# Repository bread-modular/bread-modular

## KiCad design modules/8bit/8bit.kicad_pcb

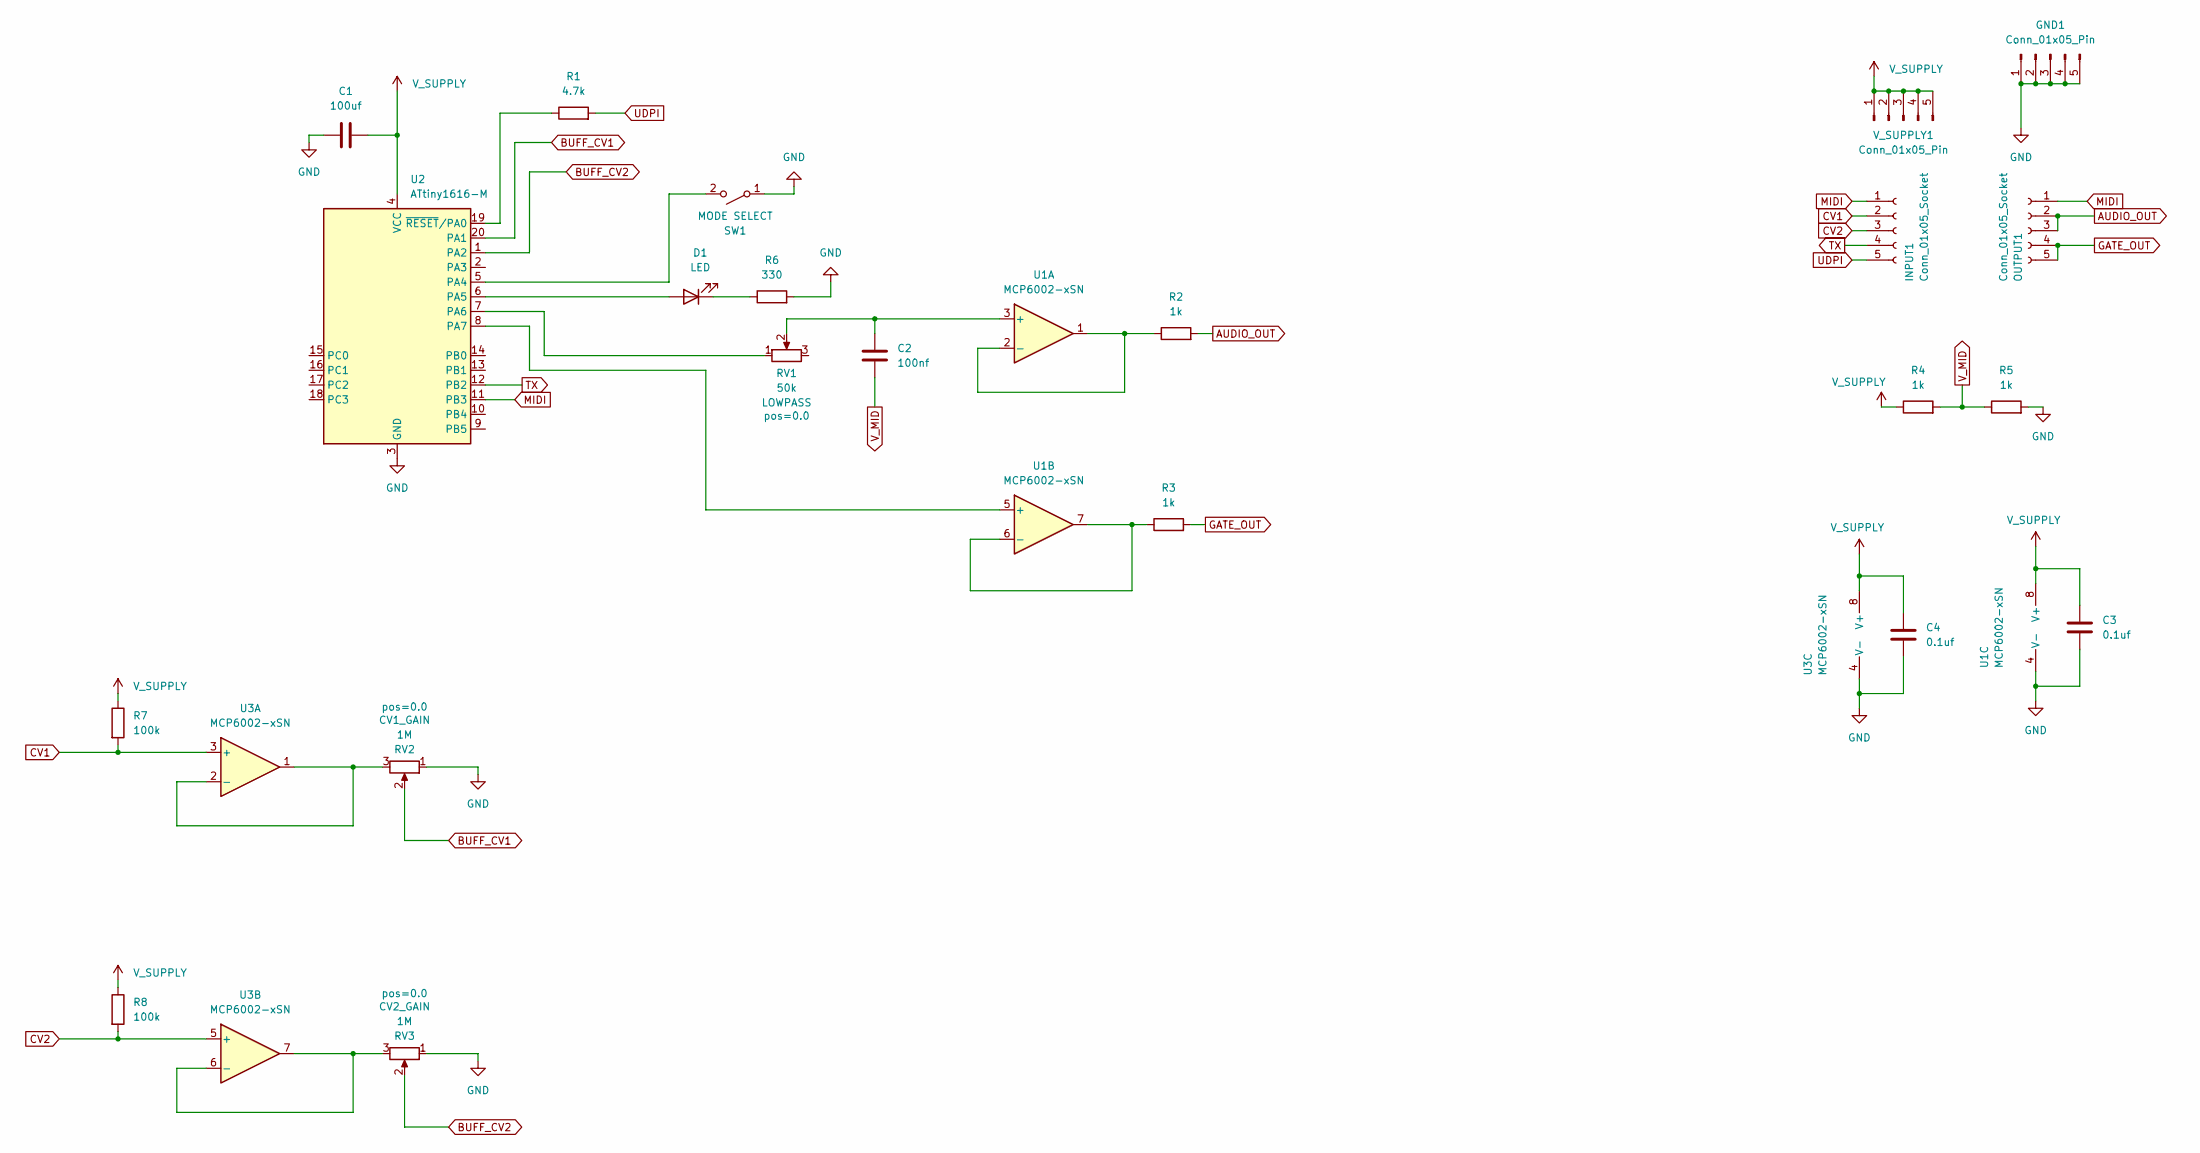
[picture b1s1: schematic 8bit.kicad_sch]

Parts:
C1: 100uf; C_1206_3216Metric
C2: 100nf; C_0402_1005Metric
C3, C4: 0.1uf; C_0402_1005Metric
D1: LED; LED_0603_1608Metric
GND1: Conn_01x05_Pin; Power_Connector
INPUT1: Conn_01x05_Socket; PinSocket_1x05_P2.54mm_Vertical
OUTPUT1: Conn_01x05_Socket; PinSocket_1x05_P2.54mm_Vertical
R1: 4.7k; R_0402_1005Metric
R2, R3, R4, R5: 1k; R_0402_1005Metric
R6: 330; R_0402_1005Metric
R7, R8: 100k; R_0402_1005Metric
RV1: 50k; Potentiometer_RV09
RV2, RV3: 1M; Potentiometer_RV09
SW1: MODE SELECT; SPST_TS-1187A-B-A-B
U1, U3: MCP6002-xSN; SOIC-8-1EP_3.9x4.9mm_P1.27mm_EP2.29x3mm
U2: ATtiny1616-M; VQFN-20-1EP_3x3mm_P0.4mm_EP1.7x1.7mm
V_SUPPLY1: Conn_01x05_Pin; Power_Connector

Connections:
AUDIO_OUT: OUTPUT1.2, OUTPUT1.3, R2.2
BUFF_CV1: RV2.2, U2.20 (PA1)
BUFF_CV2: RV3.2, U2.1 (PA2)
CV1: INPUT1.2, R7.2, U3.3 (+)
CV2: INPUT1.3, R8.2, U3.5 (+)
GATE_OUT: OUTPUT1.4, OUTPUT1.5, R3.2
GND: C1.1, C3.2, C4.2, GND1.1, GND1.2, GND1.3, GND1.4, GND1.5, R5.2, R6.2, RV2.1, RV3.1, SW1.1 (A), U1.4 (V-), U2.3 (GND), U2.21 (GND), U3.4 (V-)
MIDI: INPUT1.1, OUTPUT1.1, U2.11 (PB3)
unnamed: D1.2 (A), U2.6 (PA5)
unnamed: D1.1 (K), R6.1
unnamed: SW1.2 (B), U2.5 (PA4)
unnamed: C2.2, RV1.2, U1.3 (+)
unnamed: R2.1, U1.1, U1.2 (-)
unnamed: U1.5 (+), U2.8 (PA7)
unnamed: R3.1, U1.6 (-), U1.7
unnamed: RV1.1, U2.7 (PA6)
unnamed: R1.1, U2.19 (~RESET/PA0)
unnamed: RV2.3, U3.1, U3.2 (-)
unnamed: RV3.3, U3.6 (-), U3.7
TX: INPUT1.4, U2.12 (PB2)
UDPI: INPUT1.5, R1.2
V_MID: C2.1, R4.2, R5.1
V_SUPPLY: C1.2, C3.1, C4.1, R4.1, R7.1, R8.1, U1.8 (V+), U2.4 (VCC), U3.8 (V+), V_SUPPLY1.1, V_SUPPLY1.2, V_SUPPLY1.3, V_SUPPLY1.4, V_SUPPLY1.5

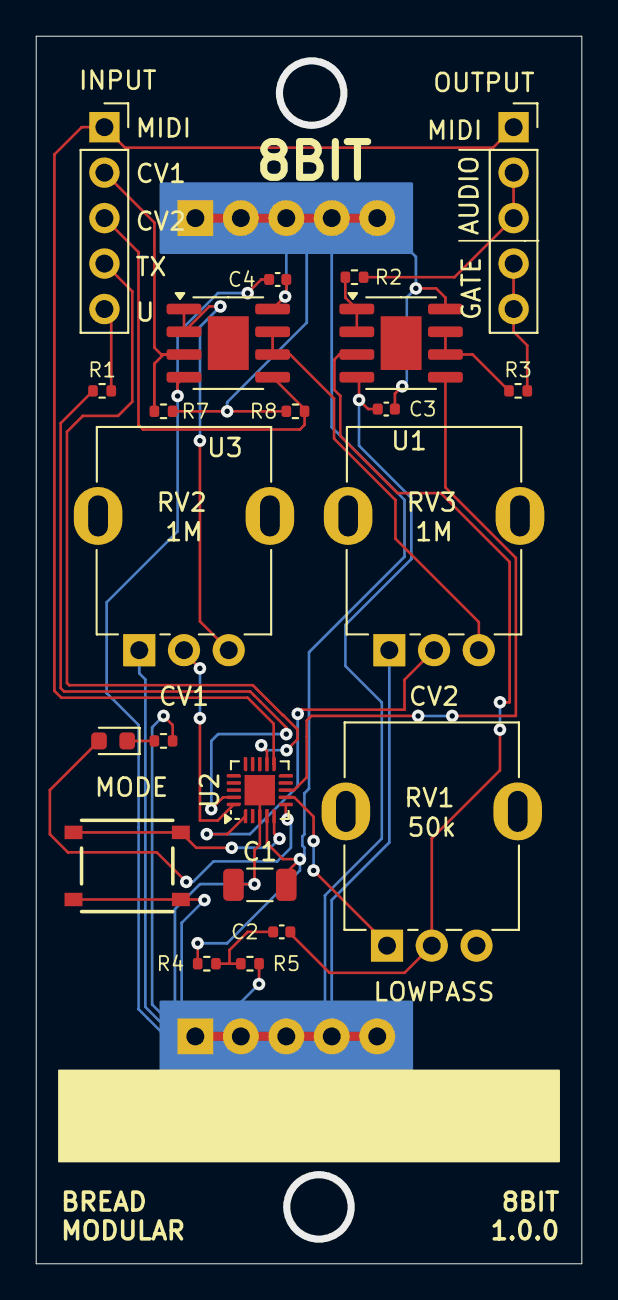
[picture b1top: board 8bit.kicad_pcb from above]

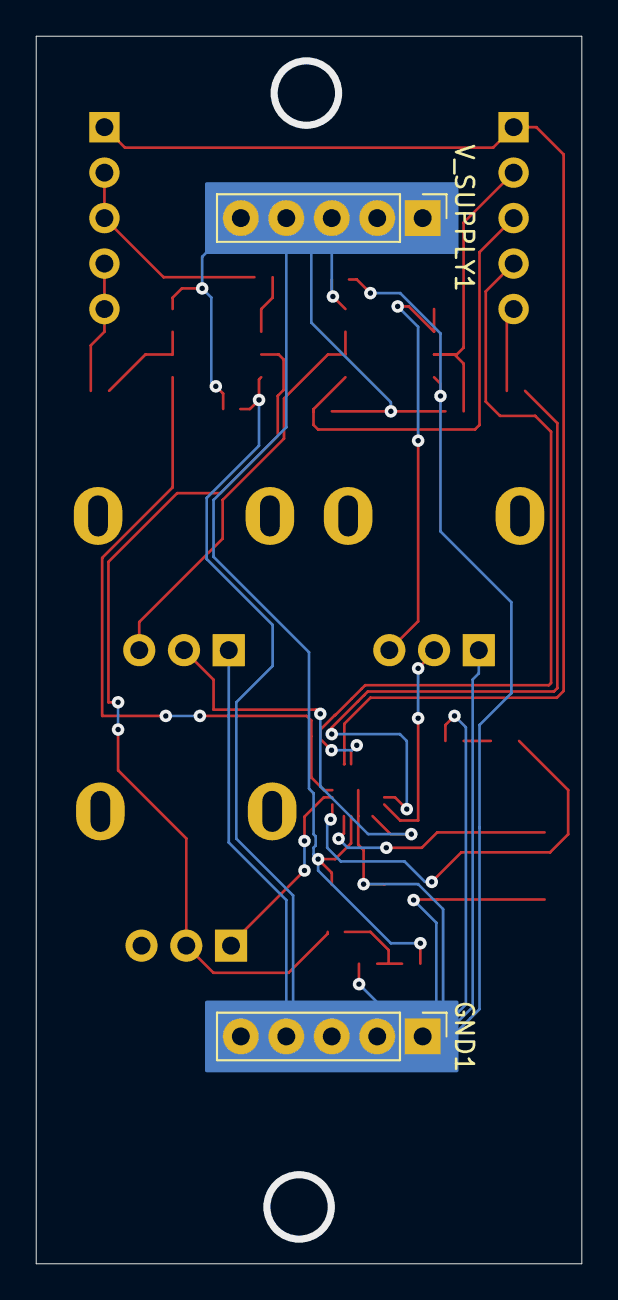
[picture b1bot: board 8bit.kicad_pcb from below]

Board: 2 copper layers, 30.5 x 68.6 mm, 24 parts (2 on the bottom side), 23 nets.

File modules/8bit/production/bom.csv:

Designator,Footprint,Quantity,Value,LCSC Part #
C1,1206,1,100uf,
C2,0402,1,100nf,
"C3, C4",0402,2,0.1uf,
D1,0603,1,LED,
"GND1, V_SUPPLY1",Power_Connector,2,Conn_01x05_Pin,
"INPUT1, OUTPUT1",PinSocket_1x05_P2.54mm_Vertical,2,Conn_01x05_Socket,
R1,0402,1,4.7k,
"R2, R3, R4, R5",0402,4,1k,
R6,0402,1,330,
"R7, R8",0402,2,100k,
RV1,Potentiometer_RV09,1,50k,
"RV2, RV3",Potentiometer_RV09,2,1M,
SW1,SPST_TS-1187A-B-A-B,1,MODE SELECT,
"U1, U3",SOIC-8-1EP_3.9x4.9mm_P1.27mm_EP2.29x3mm,2,MCP6002-xSN,
U2,VQFN-20-1EP_3x3mm_P0.4mm_EP1.7x1.7mm,1,ATtiny1616-M,

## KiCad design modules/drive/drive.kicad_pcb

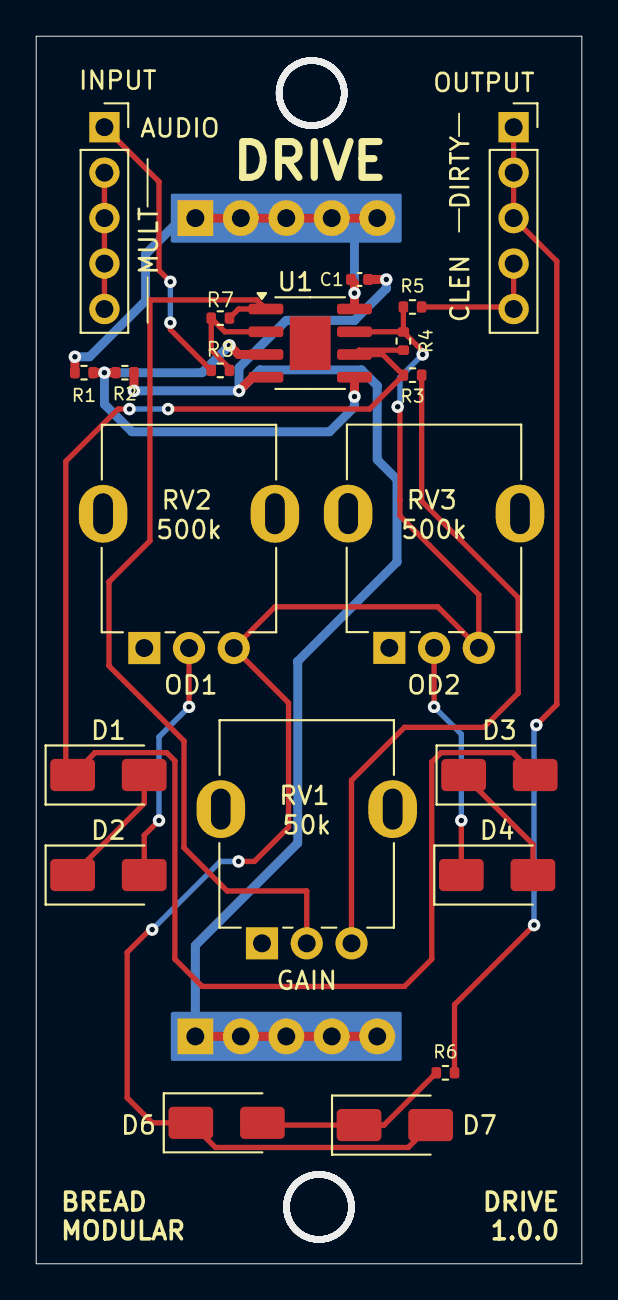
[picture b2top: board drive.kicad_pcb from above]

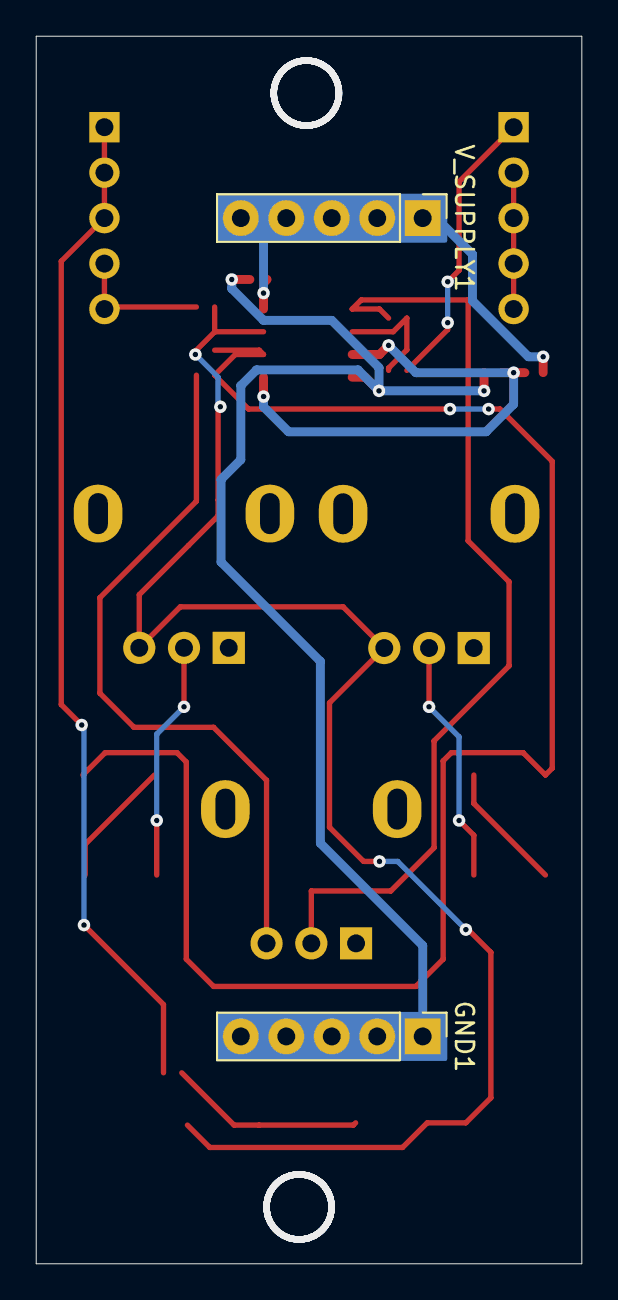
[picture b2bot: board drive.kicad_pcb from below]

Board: 2 copper layers, 30.5 x 68.6 mm, 23 parts (2 on the bottom side), 17 nets.

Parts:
C1: 0.1uf; C_0402_1005Metric
D1, D2, D3, D4, D7: SS14; D_SMA
D6: SS210; D_SMA
GND1: Conn_01x05_Pin; Power_Connector
INPUT1: Conn_01x05_Socket; PinSocket_1x05_P2.54mm_Vertical
OUTPUT1: Conn_01x05_Socket; PinSocket_1x05_P2.54mm_Vertical
R1, R2, R3, R5, R6: 1k; R_0402_1005Metric
R4: 51k; R_0402_1005Metric
R7, R8: 100k; R_0402_1005Metric
RV1: 50k; Potentiometer_RV09
RV2, RV3: 500k; Potentiometer_RV09
U1: MCP6002-xSN; SOIC-8-1EP_3.9x4.9mm_P1.27mm_EP2.29x3mm
V_SUPPLY1: Conn_01x05_Pin; Power_Connector

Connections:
AUDIO_IN: INPUT1.1, R8.1
AUDIO_OUT_CLEAN: OUTPUT1.4, OUTPUT1.5, R5.2
AUDIO_OUT_DIRTY: OUTPUT1.1, OUTPUT1.2, OUTPUT1.3, R6.2
GND: C1.2, GND1.1, GND1.2, GND1.3, GND1.4, GND1.5, R2.2, U1.4 (V-)
unnamed: D1.2 (A), D2.1 (K)
unnamed: D1.1 (K), D3.2 (A), R3.2, R4.1, U1.6 (-)
unnamed: D2.2 (A), RV2.2
unnamed: D3.1 (K), D4.2 (A)
unnamed: D4.1 (K), RV3.2
unnamed: D6.2 (A), D7.1 (K), R6.1
unnamed: D6.1 (K), D7.2 (A), R4.2, R5.1, RV2.3, RV3.3, U1.7
unnamed: INPUT1.2, INPUT1.3, INPUT1.4, INPUT1.5
unnamed: R3.1, RV1.3
unnamed: R7.2, RV1.2, U1.1
unnamed: R7.1, R8.2, U1.2 (-)
V_MID: R1.2, R2.1, U1.3 (+), U1.5 (+)
V_SUPPLY: C1.1, R1.1, U1.8 (V+), V_SUPPLY1.1, V_SUPPLY1.2, V_SUPPLY1.3, V_SUPPLY1.4, V_SUPPLY1.5

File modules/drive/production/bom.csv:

Designator,Footprint,Quantity,Value,LCSC Part #
C1,0402,1,0.1uf,
"D1, D2, D3, D4, D7",D_SMA,5,SS14,
D6,D_SMA,1,SS210,
"GND1, V_SUPPLY1",Power_Connector,2,Conn_01x05_Pin,
"INPUT1, OUTPUT1",PinSocket_1x05_P2.54mm_Vertical,2,Conn_01x05_Socket,
"R1, R2, R3, R5, R6",0402,5,1k,
R4,0402,1,51k,
"R7, R8",0402,2,100k,
RV1,Potentiometer_RV09,1,50k,
"RV2, RV3",Potentiometer_RV09,2,500k,
U1,SOIC-8-1EP_3.9x4.9mm_P1.27mm_EP2.29x3mm,1,MCP6002-xSN,

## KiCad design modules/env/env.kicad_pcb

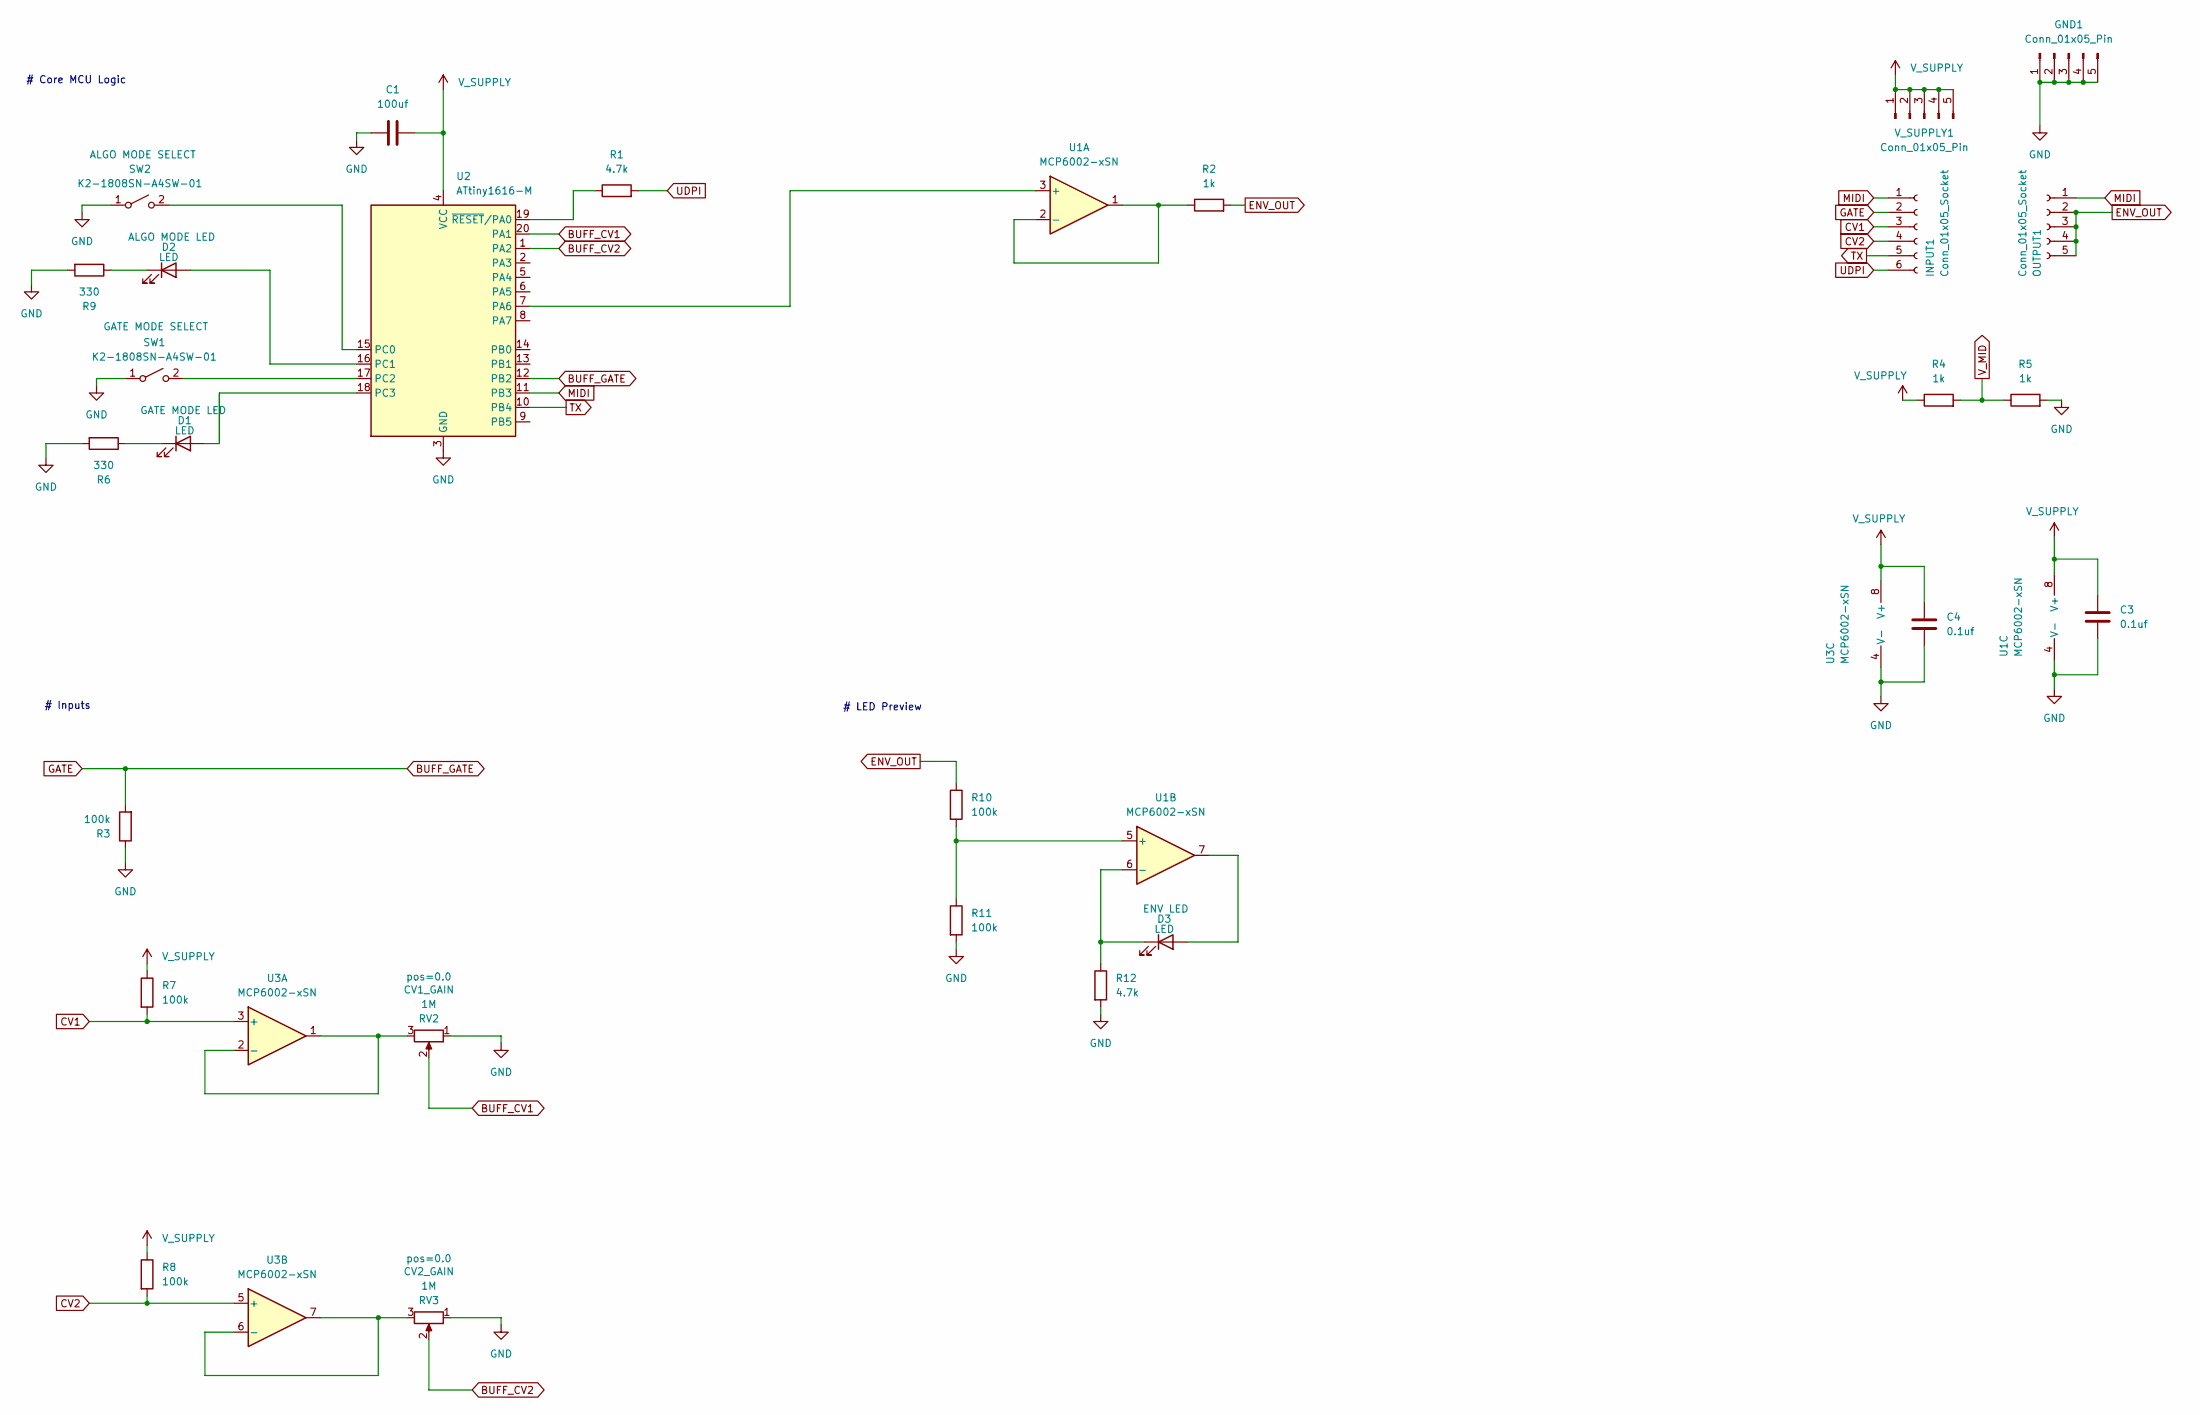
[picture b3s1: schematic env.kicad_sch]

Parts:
C1: 100uf; C_1206_3216Metric
C3, C4: 0.1uf; C_0402_1005Metric
D1, D2, D3: LED; LED_0603_1608Metric
GND1: Conn_01x05_Pin; Power_Connector
INPUT1: Conn_01x05_Socket; PinSocket_1x06_P2.54mm_Vertical
OUTPUT1: Conn_01x05_Socket; PinSocket_1x05_P2.54mm_Vertical
R1, R12: 4.7k; R_0402_1005Metric
R2, R4, R5: 1k; R_0402_1005Metric
R3, R7, R8, R10, R11: 100k; R_0402_1005Metric
R6, R9: 330; R_0402_1005Metric
RV2, RV3: 1M; Potentiometer_RV09
SW1, SW2: K2-1808SN-A4SW-01
U1, U3: MCP6002-xSN; SOIC-8-1EP_3.9x4.9mm_P1.27mm_EP2.29x3mm
U2: ATtiny1616-M; VQFN-20-1EP_3x3mm_P0.4mm_EP1.7x1.7mm
V_SUPPLY1: Conn_01x05_Pin; Power_Connector

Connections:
BUFF_CV1: RV2.2, U2.20 (PA1)
BUFF_CV2: RV3.2, U2.1 (PA2)
BUFF_GATE: INPUT1.2, R3.2, U2.12 (PB2)
CV1: INPUT1.3, R7.2, U3.3 (+)
CV2: INPUT1.4, R8.2, U3.5 (+)
ENV_OUT: OUTPUT1.2, OUTPUT1.3, OUTPUT1.4, OUTPUT1.5, R2.2, R10.1
GND: C1.1, C3.2, C4.2, GND1.1, GND1.2, GND1.3, GND1.4, GND1.5, R3.1, R5.2, R6.2, R9.2, R11.2, R12.2, RV2.1, RV3.1, SW1.1 (A), SW2.1 (A), U1.4 (V-), U2.3 (GND), U2.21 (GND), U3.4 (V-)
MIDI: INPUT1.1, OUTPUT1.1, U2.11 (PB3)
unnamed: D1.2 (A), U2.18 (PC3)
unnamed: D1.1 (K), R6.1
unnamed: D2.2 (A), U2.16 (PC1)
unnamed: D2.1 (K), R9.1
unnamed: D3.2 (A), U1.7
unnamed: D3.1 (K), R12.1, U1.6 (-)
unnamed: SW1.2 (B), U2.17 (PC2)
unnamed: SW2.2 (B), U2.15 (PC0)
unnamed: U1.3 (+), U2.7 (PA6)
unnamed: R2.1, U1.1, U1.2 (-)
unnamed: R10.2, R11.1, U1.5 (+)
unnamed: R1.1, U2.19 (~RESET/PA0)
unnamed: RV2.3, U3.1, U3.2 (-)
unnamed: RV3.3, U3.6 (-), U3.7
TX: INPUT1.5, U2.10 (PB4)
UDPI: INPUT1.6, R1.2
V_MID: R4.2, R5.1
V_SUPPLY: C1.2, C3.1, C4.1, R4.1, R7.1, R8.1, U1.8 (V+), U2.4 (VCC), U3.8 (V+), V_SUPPLY1.1, V_SUPPLY1.2, V_SUPPLY1.3, V_SUPPLY1.4, V_SUPPLY1.5

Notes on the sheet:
# LED Preview
# Core MCU Logic
# Inputs

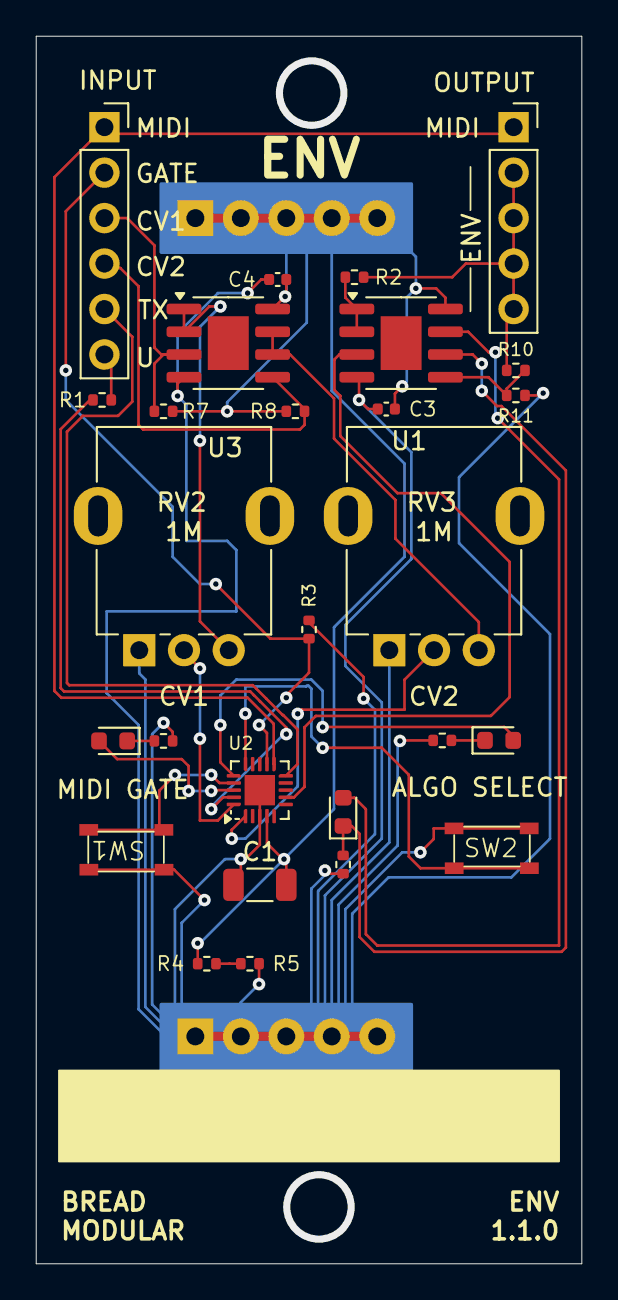
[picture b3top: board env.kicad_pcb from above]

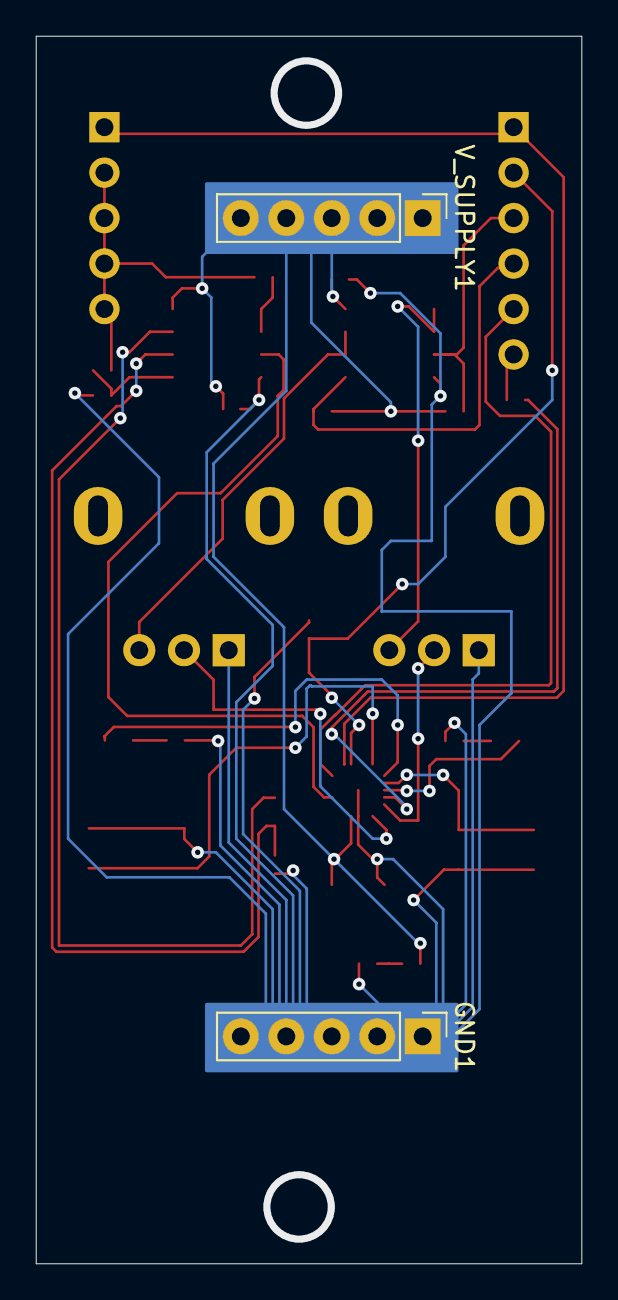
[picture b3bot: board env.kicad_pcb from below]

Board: 2 copper layers, 30.5 x 68.6 mm, 29 parts (2 on the bottom side), 26 nets.

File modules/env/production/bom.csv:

Designator,Footprint,Quantity,Value,LCSC Part #
C1,1206,1,100uf,
"C3, C4",0402,2,0.1uf,
"D1, D2, D3",0603,3,LED,
"GND1, V_SUPPLY1",Power_Connector,2,Conn_01x05_Pin,
INPUT1,PinSocket_1x06_P2.54mm_Vertical,1,Conn_01x05_Socket,
OUTPUT1,PinSocket_1x05_P2.54mm_Vertical,1,Conn_01x05_Socket,
"R1, R12",0402,2,4.7k,
"R10, R11, R3, R7, R8",0402,5,100k,
"R2, R4, R5",0402,3,1k,
"R6, R9",0402,2,330,
"RV2, RV3",Potentiometer_RV09,2,1M,
"SW1, SW2",K2-1808SN-A4SW-01,2,K2-1808SN-A4SW-01,
"U1, U3",SOIC-8-1EP_3.9x4.9mm_P1.27mm_EP2.29x3mm,2,MCP6002-xSN,
U2,VQFN-20-1EP_3x3mm_P0.4mm_EP1.7x1.7mm,1,ATtiny1616-M,

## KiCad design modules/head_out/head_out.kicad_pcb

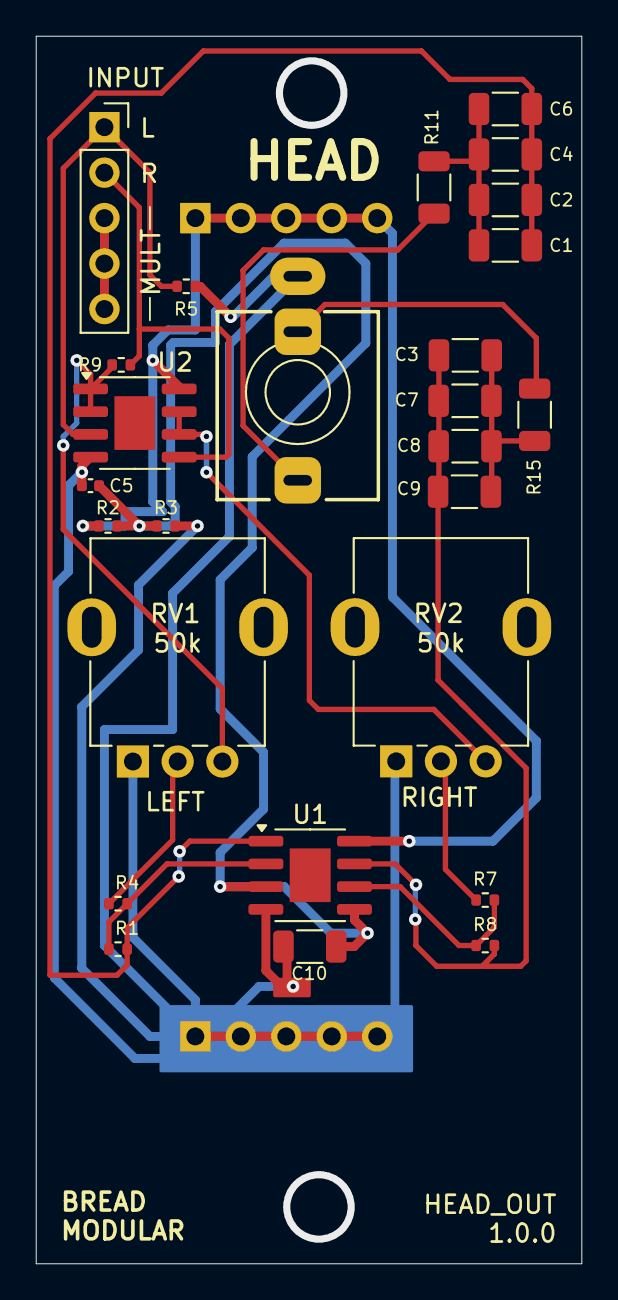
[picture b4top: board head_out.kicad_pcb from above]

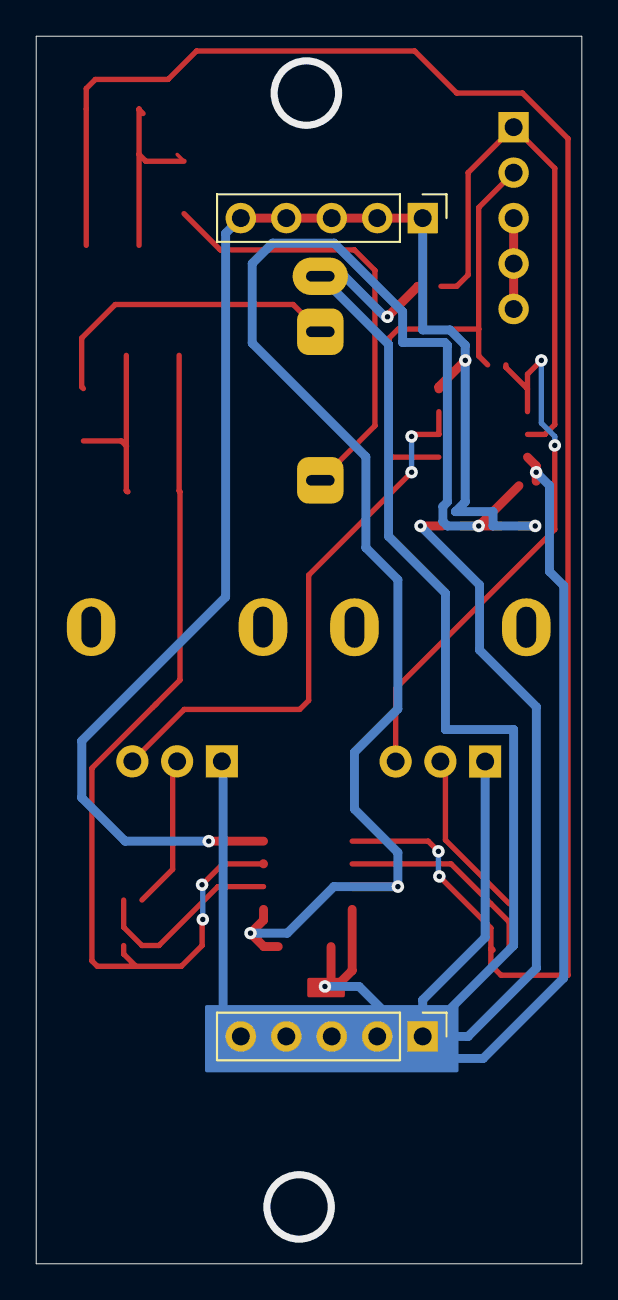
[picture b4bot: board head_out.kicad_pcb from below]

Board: 2 copper layers, 30.5 x 68.6 mm, 28 parts (2 on the bottom side), 18 nets.

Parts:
5V1: Conn_01x05_Pin; PinHeader_1x05_P2.54mm_Vertical
C1, C2, C3, C4, C6, C7, C8, C9, C10: 100uf; C_1206_3216Metric
C5: 0.1uf; C_0402_1005Metric
GND1: Conn_01x05_Pin; PinHeader_1x05_P2.54mm_Vertical
INPUT1: Conn_01x05_Socket; PinSocket_1x05_P2.54mm_Vertical
J1: AudioJack3; Jack_3.5mm_QingPu_WQP-PJ366ST_Vertical
R1, R4, R5, R7, R8: 100k; R_0402_1005Metric
R2, R3: 1k; R_0402_1005Metric
R9: 1M; R_0402_1005Metric
R11, R15: 10; R_1206_3216Metric
RV1, RV2: 50k; Potentiometer_RV09
U1, U2: MCP6002-xSN; SOIC-8-1EP_3.9x4.9mm_P1.27mm_EP2.29x3mm

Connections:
+2.5V: C5.2, C10.2, R2.2, R3.1, U1.3 (+), U1.5 (+)
GND: C5.1, C10.1, GND1.1, GND1.2, GND1.3, GND1.4, GND1.5, J1.S, R3.2, R5.2, RV1.1, RV2.1, U1.4 (V-), U2.4 (V-)
IN_L: INPUT1.1, R5.1, U2.3 (+)
IN_R: INPUT1.2, R9.2, U2.5 (+)
unnamed: C1.1, C2.1, C4.1, C6.1, R1.2, U1.1
unnamed: C1.2, C2.2, C4.2, C6.2, R11.2
unnamed: C3.1, C7.1, C8.1, C9.1, R8.2, U1.7
unnamed: C3.2, C7.2, C8.2, C9.2, R15.2
unnamed: INPUT1.3, INPUT1.4, INPUT1.5
unnamed: R4.1, RV1.2
unnamed: R7.1, RV2.2
unnamed: R1.1, R4.2, U1.2 (-)
unnamed: R7.2, R8.1, U1.6 (-)
unnamed: R9.1, RV1.3, U2.1, U2.2 (-)
unnamed: RV2.3, U2.6 (-), U2.7
OUT_L: J1.T, R11.1
OUT_R: J1.R, R15.1
V_SUPPLY: 5V1.1, 5V1.2, 5V1.3, 5V1.4, 5V1.5, R2.1, U1.8 (V+), U2.8 (V+)

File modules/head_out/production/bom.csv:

Designator,Footprint,Quantity,Value,LCSC Part #
"5V1, GND1",PinHeader_1x05_P2.54mm_Vertical,2,Conn_01x05_Pin,
"C1, C10, C2, C3, C4, C6, C7, C8, C9",1206,9,100uf,
C5,0402,1,0.1uf,
INPUT1,PinSocket_1x05_P2.54mm_Vertical,1,Conn_01x05_Socket,
J1,Jack_3.5mm_QingPu_WQP-PJ366ST_Vertical,1,AudioJack3,
"R1, R4, R5, R7, R8",0402,5,100k,
"R11, R15",1206,2,10,
"R2, R3",0402,2,1k,
R9,0402,1,1M,
"RV1, RV2",Potentiometer_RV09,2,50k,
"U1, U2",SOIC-8-1EP_3.9x4.9mm_P1.27mm_EP2.29x3mm,2,MCP6002-xSN,
